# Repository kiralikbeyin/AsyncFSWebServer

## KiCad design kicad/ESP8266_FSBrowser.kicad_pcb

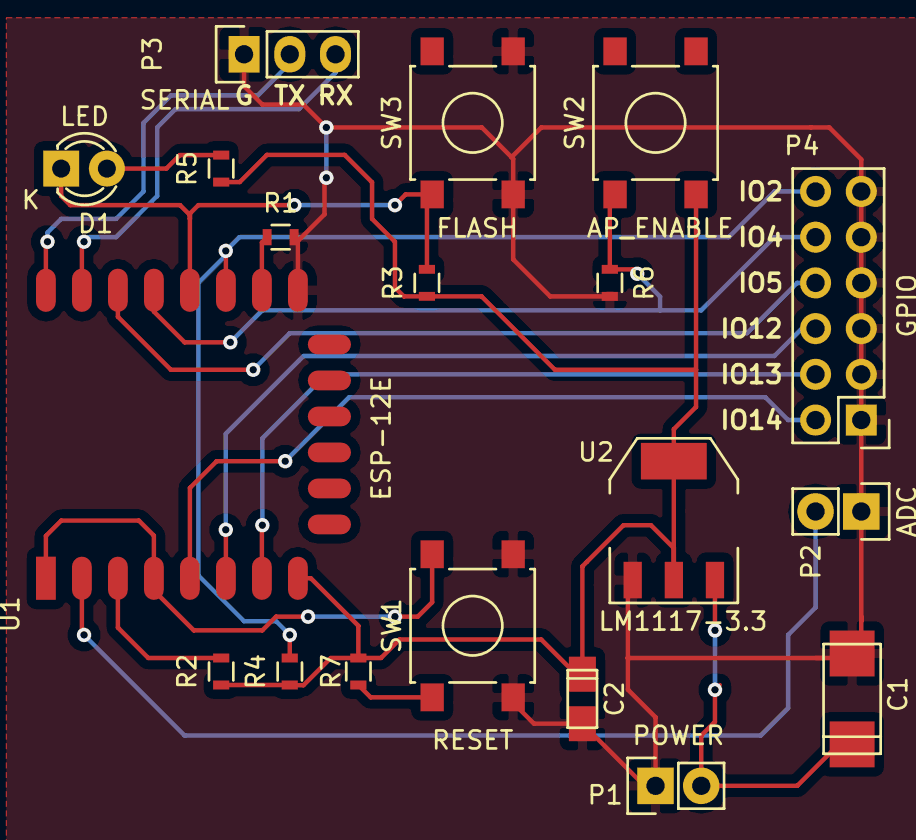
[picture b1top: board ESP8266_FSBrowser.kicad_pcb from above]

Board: 2 copper layers, 19 parts (0 on the bottom side), 17 nets.

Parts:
C1: 10u; TantalC_SizeU_EIA-6032
C2: 1u; TantalC_SizeS_EIA-3216
D1: LED; LED-3MM
P1: POWER; Pin_Header_Straight_1x02
P2: ADC; Pin_Header_Straight_1x02
P3: SERIAL; Pin_Header_Straight_1x03
P4: GPIO; Pin_Header_Straight_2x06
R1, R2, R3, R4, R6, R7: 10k; R_0603
R5: 330; R_0603
SW1: RESET; SW_SPST_B3S-1000
SW2: AP_ENABLE; SW_SPST_B3S-1000
SW3: FLASH; SW_SPST_B3S-1000
U1: ESP-12E
U2: LM1117-3.3; SOT-223

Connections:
+3V3: C2.1, R2.1, R3.1, R4.1, R5.1, R7.1, SW2.2, U1.8, U2.2, U2.4
ADC: P2.2, U1.2
AP_EN: P4.10, R6.1, SW2.1, U1.19
GND: C1.2, C2.2, P1.1, P2.1, P3.1, P4.1, P4.3, P4.5, P4.7, P4.9, P4.11, R1.2, R6.2, SW1.2, SW3.2, U1.15, U2.1
GPIO2: P4.12, R4.2, U1.17
GPIO5: P4.8, U1.20
GPIO12: P4.6, U1.6
GPIO13: P4.4, U1.7
GPIO14: P4.2, U1.5
unnamed: C1.1, P1.2, U2.3
unnamed: D1.1, R3.2, SW3.1, U1.18
unnamed: D1.2, R5.2
unnamed: P3.2, U1.22
unnamed: P3.3, U1.21
unnamed: R1.1, U1.16
unnamed: R2.2, U1.3
RST: R7.2, SW1.1, U1.1, U1.4

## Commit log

2016-08-04 First commit. Not functional
2016-08-05 no message
2016-08-05 Add Kicad files
2016-08-25 added quotes
    config.IP[0] = json["ip"][0]; TO config.IP[0] = json["ip"]["0"];
